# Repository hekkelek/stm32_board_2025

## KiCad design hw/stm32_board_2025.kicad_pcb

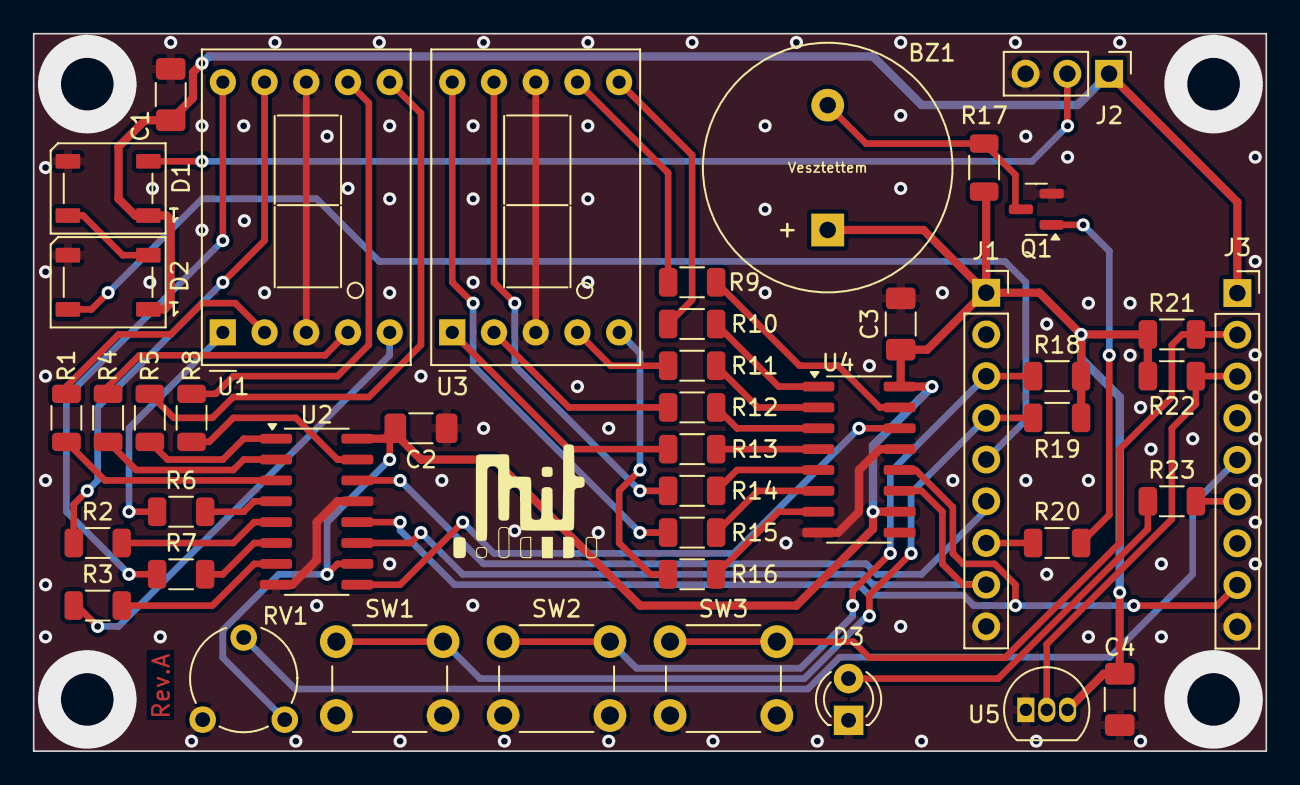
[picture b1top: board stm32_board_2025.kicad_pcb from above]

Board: 2 copper layers, 75.1 x 43.7 mm, 44 parts (0 on the bottom side), 52 nets.

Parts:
BZ1: Buzzer; Buzzer_15x7.5RM7.6
C1, C2, C3, C4: 100n; C_1206_3216Metric_Pad1.33x1.80mm_HandSolder
D1, D2: WS2812B; LED_WS2812B_PLCC4_5.0x5.0mm_P3.2mm
D3: LED; LED_D3.0mm
J1, J3: Connector; PinSocket_1x09_P2.54mm_Vertical
J2: Ext. LEDs; PinHeader_1x03_P2.54mm_Vertical
Q1: MMBT3904; SOT-23
R1, R2, R3, R4, R5, R6, R7, R8, R9, R10, R11, R12, R13, R14, R15, R16, R23: 750; R_1206_3216Metric
R17, R20: 1k; R_1206_3216Metric
R18, R19, R21: 10k; R_1206_3216Metric
R22: 4,7k; R_1206_3216Metric
RV1: 10k; Potentiometer_Piher_PT-6-V_Vertical
SW1, SW2, SW3: SW_Push; SW_PUSH_6mm
U1, U3: D198K; D1X8K
U2, U4: 74HC595; SOIC-16_3.9x9.9mm_P1.27mm
U5: DS18B20; TO-92_Inline

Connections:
+3.3V: BZ1.1 (-), C2.1, C3.1, C4.1, J1.1, R17.1, R18.1, R19.1, R21.1, R22.2, RV1.1, U2.10 (~SRCLR), U2.16 (VCC), U4.10 (~SRCLR), U4.16 (VCC), U5.3 (V_{DD})
+5V: C1.1, D1.1 (VDD), D2.1 (VDD), J2.1, J3.1
/PA0: J3.5, RV1.2
/PA1: J3.6, R23.1
/PA4: J3.8, U2.12 (RCLK), U4.12 (RCLK)
/PA5: J1.8, U2.11 (SRCLK), U4.11 (SRCLK)
/PA6: J1.7, R20.2
/PA7: J1.6, U2.14 (SER)
/PA9: J1.4, R19.2, SW1.1
/PA10: J1.3, R18.2, SW2.1
/PB1: D2.4 (DIN), J1.5
/PF0: J3.2, R21.2, SW3.1
/PF1: J3.3, R22.1, U5.2 (DQ)
GND: C1.2, C2.2, C3.2, C4.2, D1.3 (VSS), D2.3 (VSS), D3.1 (K), J1.9, J2.3, J3.9, Q1.2 (E), RV1.3, SW1.2, SW2.2, SW3.2, U1.3 (CC), U1.8 (CC), U2.8 (GND), U2.13 (~OE), U3.3 (CC), U3.8 (CC), U4.8 (GND), U4.13 (~OE), U5.1 (GND)
unnamed: BZ1.2 (+), Q1.3 (C), R17.2
unnamed: D3.2 (A), R23.2
unnamed: D1.4 (DIN), D2.2 (DOUT)
unnamed: D1.2 (DOUT), J2.2
unnamed: Q1.1 (B), R20.1
unnamed: R8.1, U2.15 (QA)
unnamed: R5.1, U2.1 (QB)
unnamed: R4.1, U2.2 (QC)
unnamed: R1.1, U2.3 (QD)
unnamed: R6.1, U2.4 (QE)
unnamed: R2.1, U2.5 (QF)
unnamed: R7.1, U2.6 (QG)
unnamed: U2.9 (QH'), U4.14 (SER)
unnamed: R3.1, U2.7 (QH)
unnamed: R9.1, U4.15 (QA)
unnamed: R10.1, U4.1 (QB)
unnamed: R11.1, U4.2 (QC)
unnamed: R12.1, U4.3 (QD)
unnamed: R13.1, U4.4 (QE)
unnamed: R14.1, U4.5 (QF)
unnamed: R15.1, U4.6 (QG)
unnamed: R16.1, U4.7 (QH)
unnamed: R8.2, U1.7 (A)
unnamed: R5.2, U1.6 (B)
unnamed: R4.2, U1.4 (C)
unnamed: R1.2, U1.2 (D)
unnamed: R3.2, U1.5 (DP)
unnamed: R6.2, U1.1 (E)
unnamed: R2.2, U1.9 (F)
unnamed: R7.2, U1.10 (G)
unnamed: R9.2, U3.7 (A)
unnamed: R10.2, U3.6 (B)
unnamed: R11.2, U3.4 (C)
unnamed: R12.2, U3.2 (D)
unnamed: R16.2, U3.5 (DP)
unnamed: R13.2, U3.1 (E)
unnamed: R14.2, U3.9 (F)
unnamed: R15.2, U3.10 (G)

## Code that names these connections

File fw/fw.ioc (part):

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Mcu.Name=STM32F070F6Px
Mcu.Package=TSSOP20
Mcu.UserName=STM32F070F6Px
PA0.Mode=IN0
PA0.Signal=ADC_IN0
PA1.Signal=GPIO_Output
PA10.Signal=GPIO_Input
PA13.Mode=Serial_Wire
PA13.Signal=SYS_SWDIO
PA14.Mode=Serial_Wire
PA14.Signal=SYS_SWCLK
PA2.Mode=Asynchronous
PA2.Signal=USART2_TX
PA3.Mode=Asynchronous
PA3.Signal=USART2_RX
PA4.Mode=NSS_Signal_Hard_Output
PA4.Signal=SPI1_NSS
PA5.Mode=TX_Only_Simplex_Unidirect_Master
PA5.Signal=SPI1_SCK
PA6.Signal=S_TIM16_CH1
PA7.Mode=TX_Only_Simplex_Unidirect_Master
PA7.Signal=SPI1_MOSI
PA9.Signal=GPIO_Input
PB1.Signal=S_TIM3_CH4
PF0-OSC_IN.Signal=GPIO_Input
PF1-OSC_OUT.Signal=GPIO_Output
board=custom

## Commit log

2025-02-21 Initial commit.
2025-02-21 Routed.
2025-02-23 Sent to fab.
